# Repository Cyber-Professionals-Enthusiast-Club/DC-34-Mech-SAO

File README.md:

# About
This repository contains design files for the CPEC SAO pluggin modules for the 
CPEC DC 34 badge. 

# Structure 
- Artis_art/ directory for art files (.svg vector graphics)
- DC34-Mech-SAO/ directory for circuit board design files (kicad 6 project)
- DC34-Mech-SAO-Firmware/ directory for the arduino file to load onto the SAO
- libraries/ directory for kicad symbols and footprint files 

## Running
To view schematics, please run KiCad 6.0.11 or later. Change directory into 
DC-34-Mech-SAO and run
```
kicad DC-34-Mech-SAO.kicad_pro
```

Please note: please run kicad from the same directory as the .kicad_pro file 
is stored because the fp-lib-table and sym-lib-table use relative paths 
so that this project is portable between computers.

# Development Rules
- No spaces in file names or directories because this causes some tools to not 
beable to load the files
- Do not check in binary files because this bloats the repo, instead generate 
them with scripts from ASCII files and add the binary extension to the 
.gitignore file

# Associated Repos
Board firmware is developed in this repo: 
[ttps://github.com/eggsactly/DcC4-Mech-SAO-Plugin-Demo](https://github.com/eggsactly/DcC4-Mech-SAO-Plugin-Demo)

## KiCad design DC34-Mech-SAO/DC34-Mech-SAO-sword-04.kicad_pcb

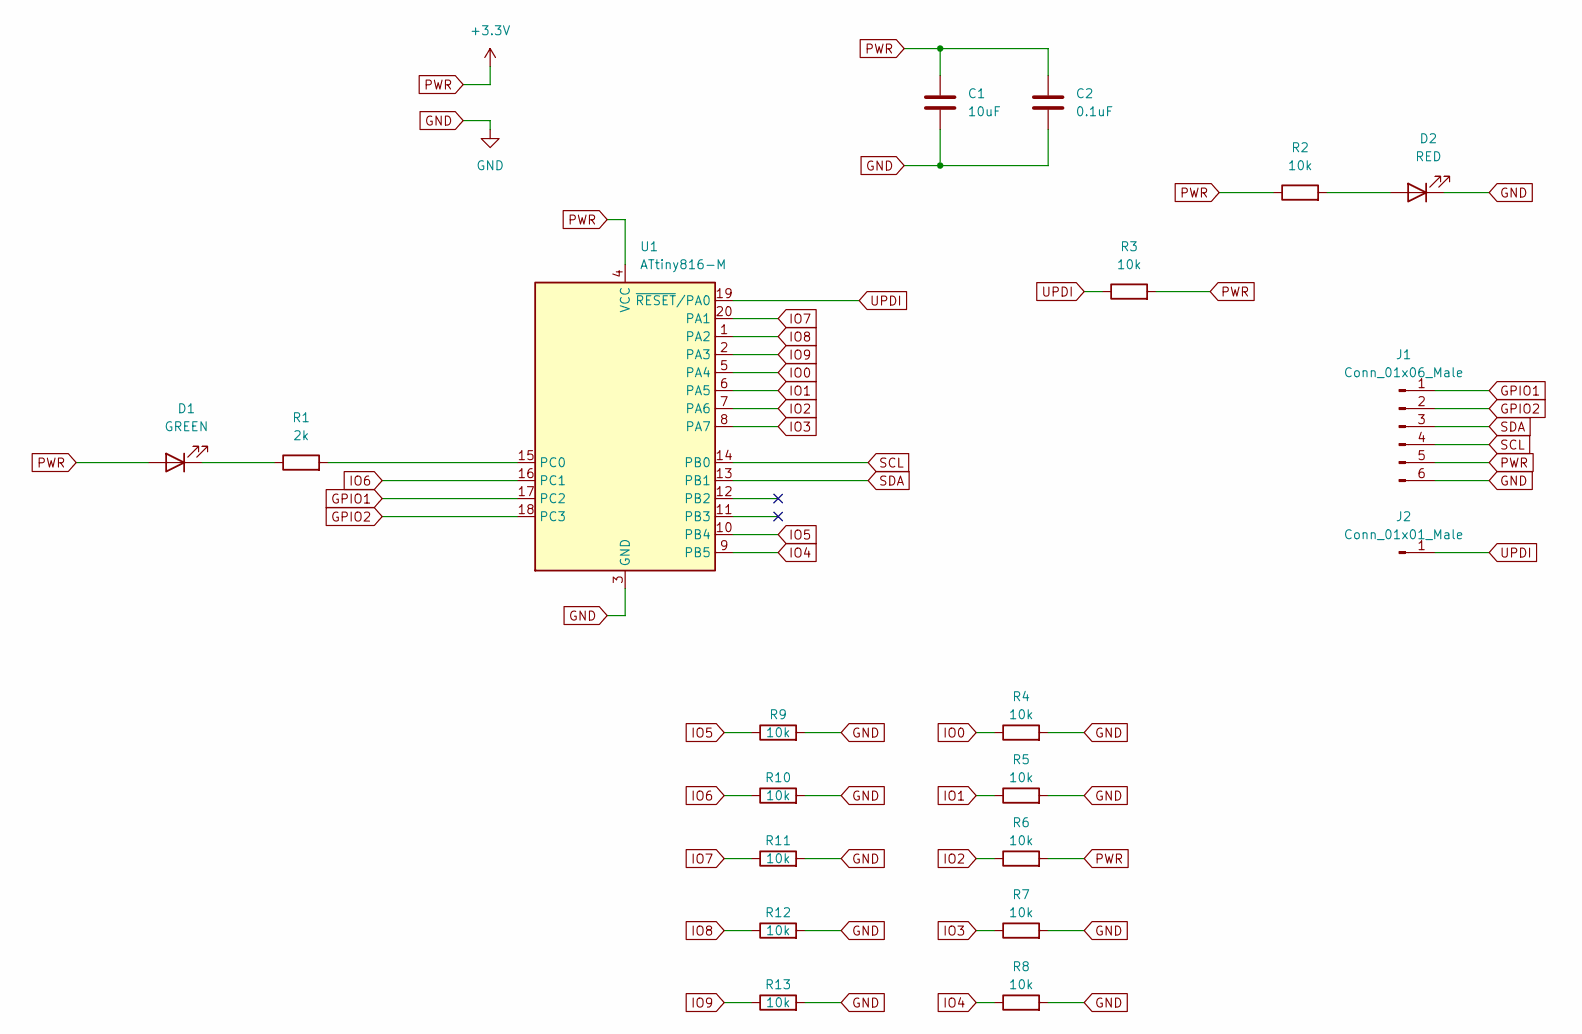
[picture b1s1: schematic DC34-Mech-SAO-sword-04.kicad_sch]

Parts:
C1: 10uF; C_0402_1005Metric
C2: 0.1uF; C_0201_0603Metric
D1: GREEN; LED_0603_1608Metric_Pad1.05x0.95mm_HandSolder
D2: RED; LED_0603_1608Metric_Pad1.05x0.95mm_HandSolder
J1: Conn_01x06_Male; PinSocket_2x03_P2.54mm_Vertical_SMD
J2: Conn_01x01_Male; Aligator_TIP
R1: 2k; R_0402_1005Metric
R2, R3, R4, R5, R6, R7, R8, R9, R10, R11, R12, R13: 10k; R_0402_1005Metric
U1: ATtiny816-M; VQFN20_3X3_MCH

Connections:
GND: C1.2, C2.2, D2.1 (K), J1.6, R4.2, R5.2, R7.2, R8.2, R9.2, R10.2, R11.2, R12.2, R13.2, U1.3 (GND), U1.21 (GND)
GPIO1: J1.1, U1.17 (PC2)
GPIO2: J1.2, U1.18 (PC3)
IO0: R4.1, U1.5 (PA4)
IO1: R5.1, U1.6 (PA5)
IO2: R6.1, U1.7 (PA6)
IO3: R7.1, U1.8 (PA7)
IO4: R8.1, U1.9 (PB5)
IO5: R9.1, U1.10 (PB4)
IO6: R10.1, U1.16 (PC1)
IO7: R11.1, U1.20 (PA1)
IO8: R12.1, U1.1 (PA2)
IO9: R13.1, U1.2 (PA3)
unnamed: D1.1 (K), R1.1
unnamed: D2.2 (A), R2.2
unnamed: R1.2, U1.15 (PC0)
PWR: C1.1, C2.1, D1.2 (A), J1.5, R2.1, R3.2, R6.2, U1.4 (VCC)
SCL: J1.4, U1.14 (PB0)
SDA: J1.3, U1.13 (PB1)
UPDI: J2.1, R3.1, U1.19 (~RESET/PA0)

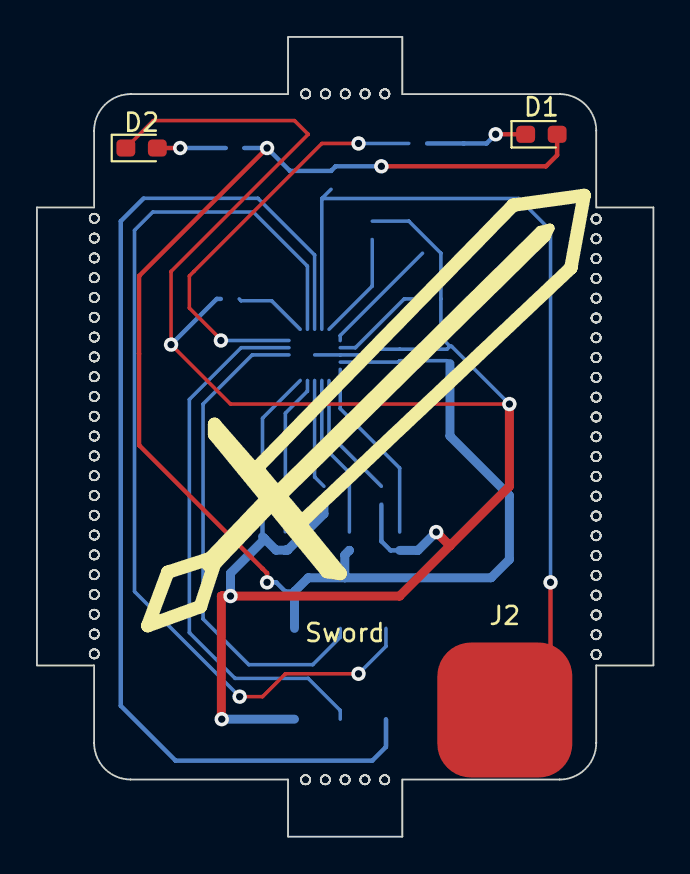
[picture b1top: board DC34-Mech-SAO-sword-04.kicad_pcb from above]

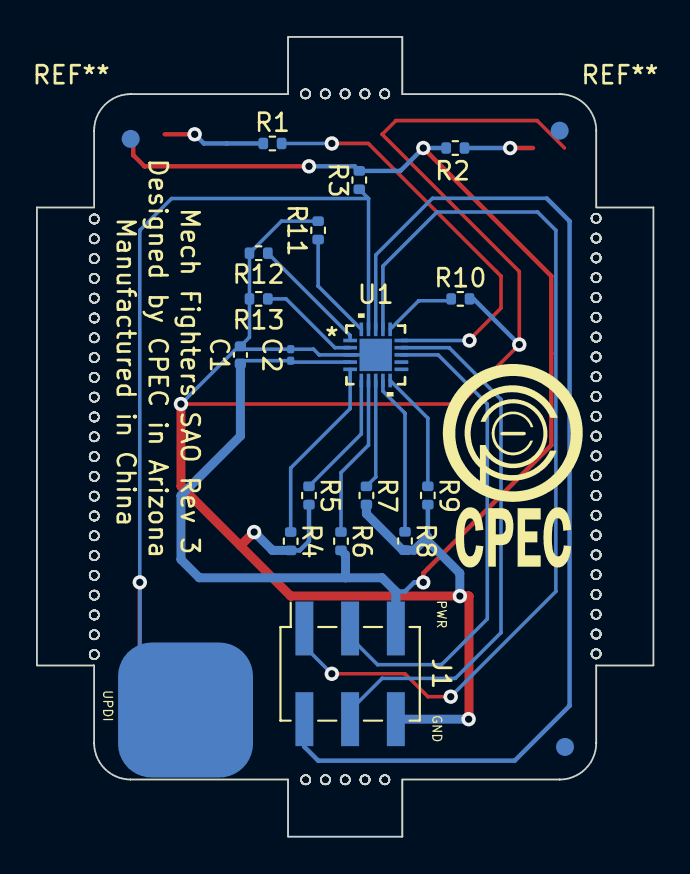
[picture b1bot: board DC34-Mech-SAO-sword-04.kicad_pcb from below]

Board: 2 copper layers, 34.2 x 44.4 mm, 20 parts (17 on the bottom side), 20 nets.

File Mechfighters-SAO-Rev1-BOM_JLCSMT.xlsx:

Comment | Designator | Footprint | JLCPCB Part #（optional）
ATTINY816-MNR | U1 | UQFN-20-EP | C2052778
10 uF | C1 | 0402 (1005 Metric) | C15525
0.1 uF | C2 | 0201 (0603 Metric) | C66938
10 K | R1, R2, R3, R4, R5, R6, R7, R8, R9, R10, R11, R12, R13 | 0402 (1005 Metric) | C22356213
LED Green | D1 | 0603 (1608 Metric) | C9900016798
LED Red | D2 | 0603 (1608 Metric) | C9900014434
DNP (Do not Populate) | J1 | N/A | N/A
DNP (Do not Populate) | J2 | N/A | N/A

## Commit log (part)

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2026-04-14 Created board design.
2026-04-20 Using ATTiny 816.
2026-04-20 Added README.
2026-04-20 Updated link.
2026-04-25 Create weapons draft1.svg
    New SVG for SAO art
    -Energy weapon
    -Missile
    -Gatling gun
2026-04-27 Removed difficult characters from folder name.
2026-04-27 Split out weapons into separate svg files.
2026-04-27 Added Development Rules section to README.
2026-04-27 change 2
    added machine gun
2026-05-01 Removed zip files.
2026-05-01 Addressed clearence issue.
2026-05-01 Added silkscreen.
2026-05-01 Added silkscreen
    Added descriptive text to board.
2026-05-04 Added BOM.
2026-05-06 Added BOM
    Added Bill of Materials for Mech SAO for JLCPCB.
2026-05-06 Create Mechfighters-SAO-Rev1-BOM_JLCSMT.xlsx
    Added Mech Fighters SAO BOM.
